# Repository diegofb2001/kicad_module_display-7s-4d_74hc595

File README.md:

# kicad_module_display-7s-4d_74hc595
Módulo para mi ESP32 con display 7 segmentos, 4 dígitos con un 74HC959.

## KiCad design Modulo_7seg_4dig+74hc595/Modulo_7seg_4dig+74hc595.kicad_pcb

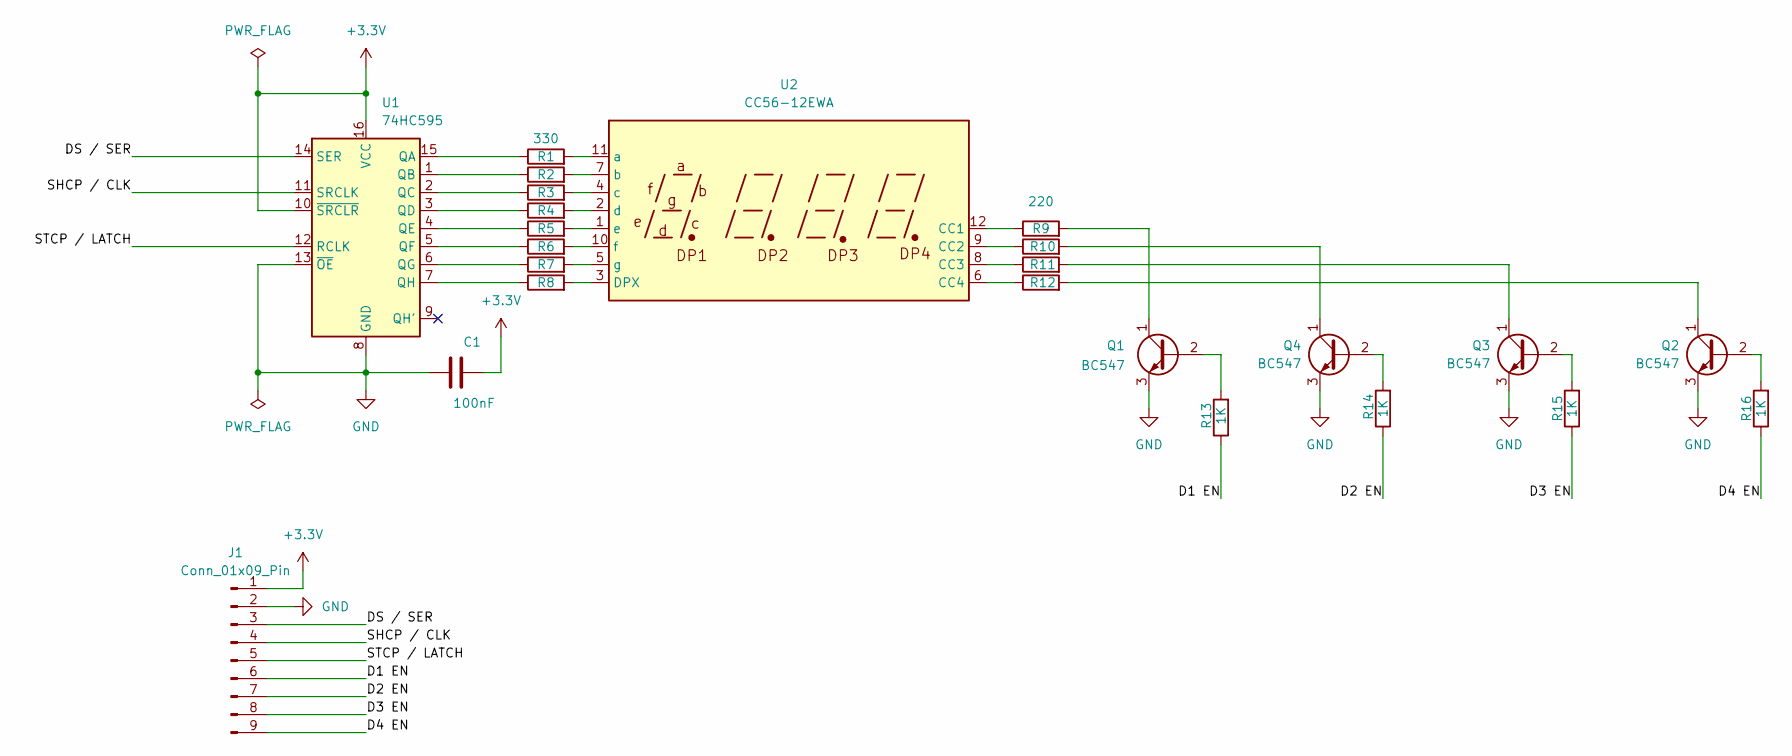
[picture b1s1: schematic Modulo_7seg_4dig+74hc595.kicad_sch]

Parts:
C1: 100nF; C_Disc_D5.0mm_W2.5mm_P5.00mm
J1: Conn_01x09_Pin; JST_EH_B9B-EH-A_1x09_P2.50mm_Vertical
Q1, Q2, Q3, Q4: BC547; TO-92_Inline
R1, R2, R3, R4, R5, R6, R7, R8: 330; R_0805_2012Metric_Pad1.20x1.40mm_HandSolder
R9, R10, R11, R12: 220; R_0805_2012Metric_Pad1.20x1.40mm_HandSolder
R13, R14, R15, R16: 1K; R_0805_2012Metric_Pad1.20x1.40mm_HandSolder
U1: 74HC595; CERDIP-16_W7.62mm_SideBrazed_LongPads
U2: CC56-12EWA; CA56-12EWA

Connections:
+3.3V: C1.2, J1.1, U1.10 (~SRCLR), U1.16 (VCC)
/D1 EN: J1.6, R13.1
/D2 EN: J1.7, R14.1
/D3 EN: J1.8, R15.1
/D4 EN: J1.9, R16.1
/DS / SER: J1.3, U1.14 (SER)
/SHCP / CLK: J1.4, U1.11 (SRCLK)
/STCP / LATCH: J1.5, U1.12 (RCLK)
GND: C1.1, J1.2, Q1.3 (E), Q2.3 (E), Q3.3 (E), Q4.3 (E), U1.8 (GND), U1.13 (~OE)
unnamed: Q1.2 (B), R13.2
unnamed: Q1.1 (C), R9.2
unnamed: Q2.2 (B), R16.2
unnamed: Q2.1 (C), R12.2
unnamed: Q3.2 (B), R15.2
unnamed: Q3.1 (C), R11.2
unnamed: Q4.2 (B), R14.2
unnamed: Q4.1 (C), R10.2
unnamed: R1.1, U1.15 (QA)
unnamed: R2.1, U1.1 (QB)
unnamed: R3.1, U1.2 (QC)
unnamed: R4.1, U1.3 (QD)
unnamed: R5.1, U1.4 (QE)
unnamed: R6.1, U1.5 (QF)
unnamed: R7.1, U1.6 (QG)
unnamed: R8.1, U1.7 (QH)
unnamed: R9.1, U2.12 (CC1)
unnamed: R10.1, U2.9 (CC2)
unnamed: R11.1, U2.8 (CC3)
unnamed: R12.1, U2.6 (CC4)
unnamed: R8.2, U2.3 (DPX)
unnamed: R1.2, U2.11 (a)
unnamed: R2.2, U2.7 (b)
unnamed: R3.2, U2.4 (c)
unnamed: R4.2, U2.2 (d)
unnamed: R5.2, U2.1 (e)
unnamed: R6.2, U2.10 (f)
unnamed: R7.2, U2.5 (g)

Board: 2 copper layers, 24 parts (0 on the bottom side), 37 nets, no tracks yet.

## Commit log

2025-12-28 Primer push con el esquema terminado y los footprint de componentes seleccionados
